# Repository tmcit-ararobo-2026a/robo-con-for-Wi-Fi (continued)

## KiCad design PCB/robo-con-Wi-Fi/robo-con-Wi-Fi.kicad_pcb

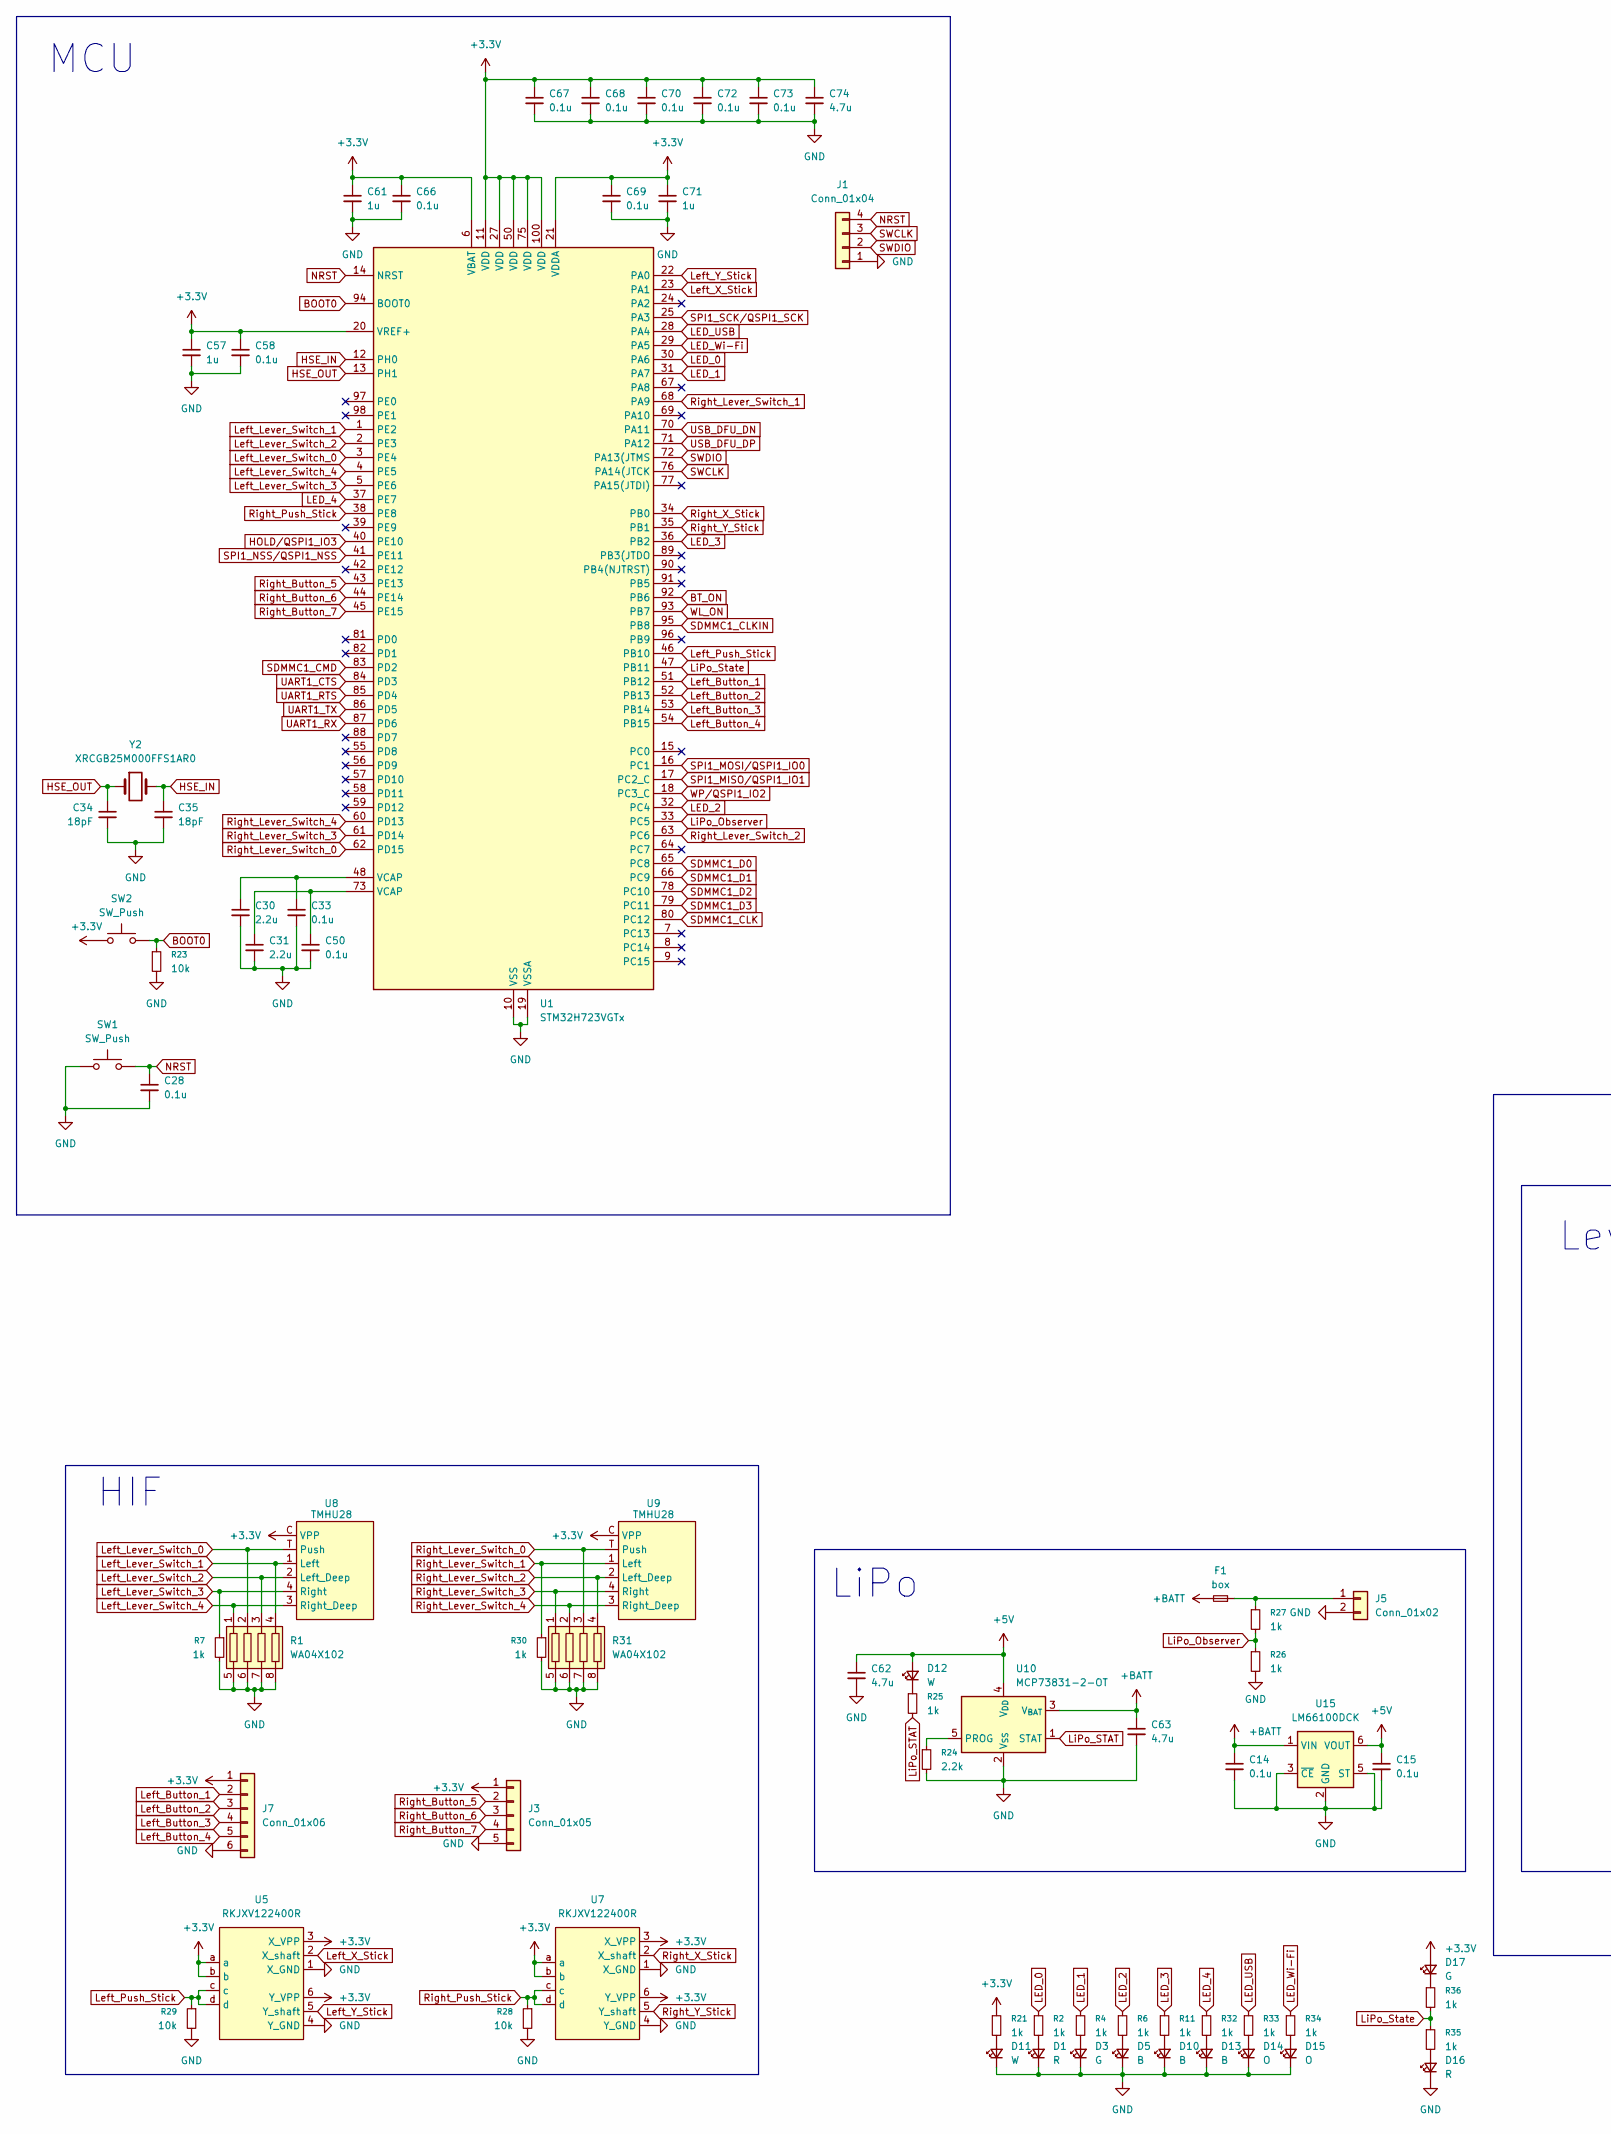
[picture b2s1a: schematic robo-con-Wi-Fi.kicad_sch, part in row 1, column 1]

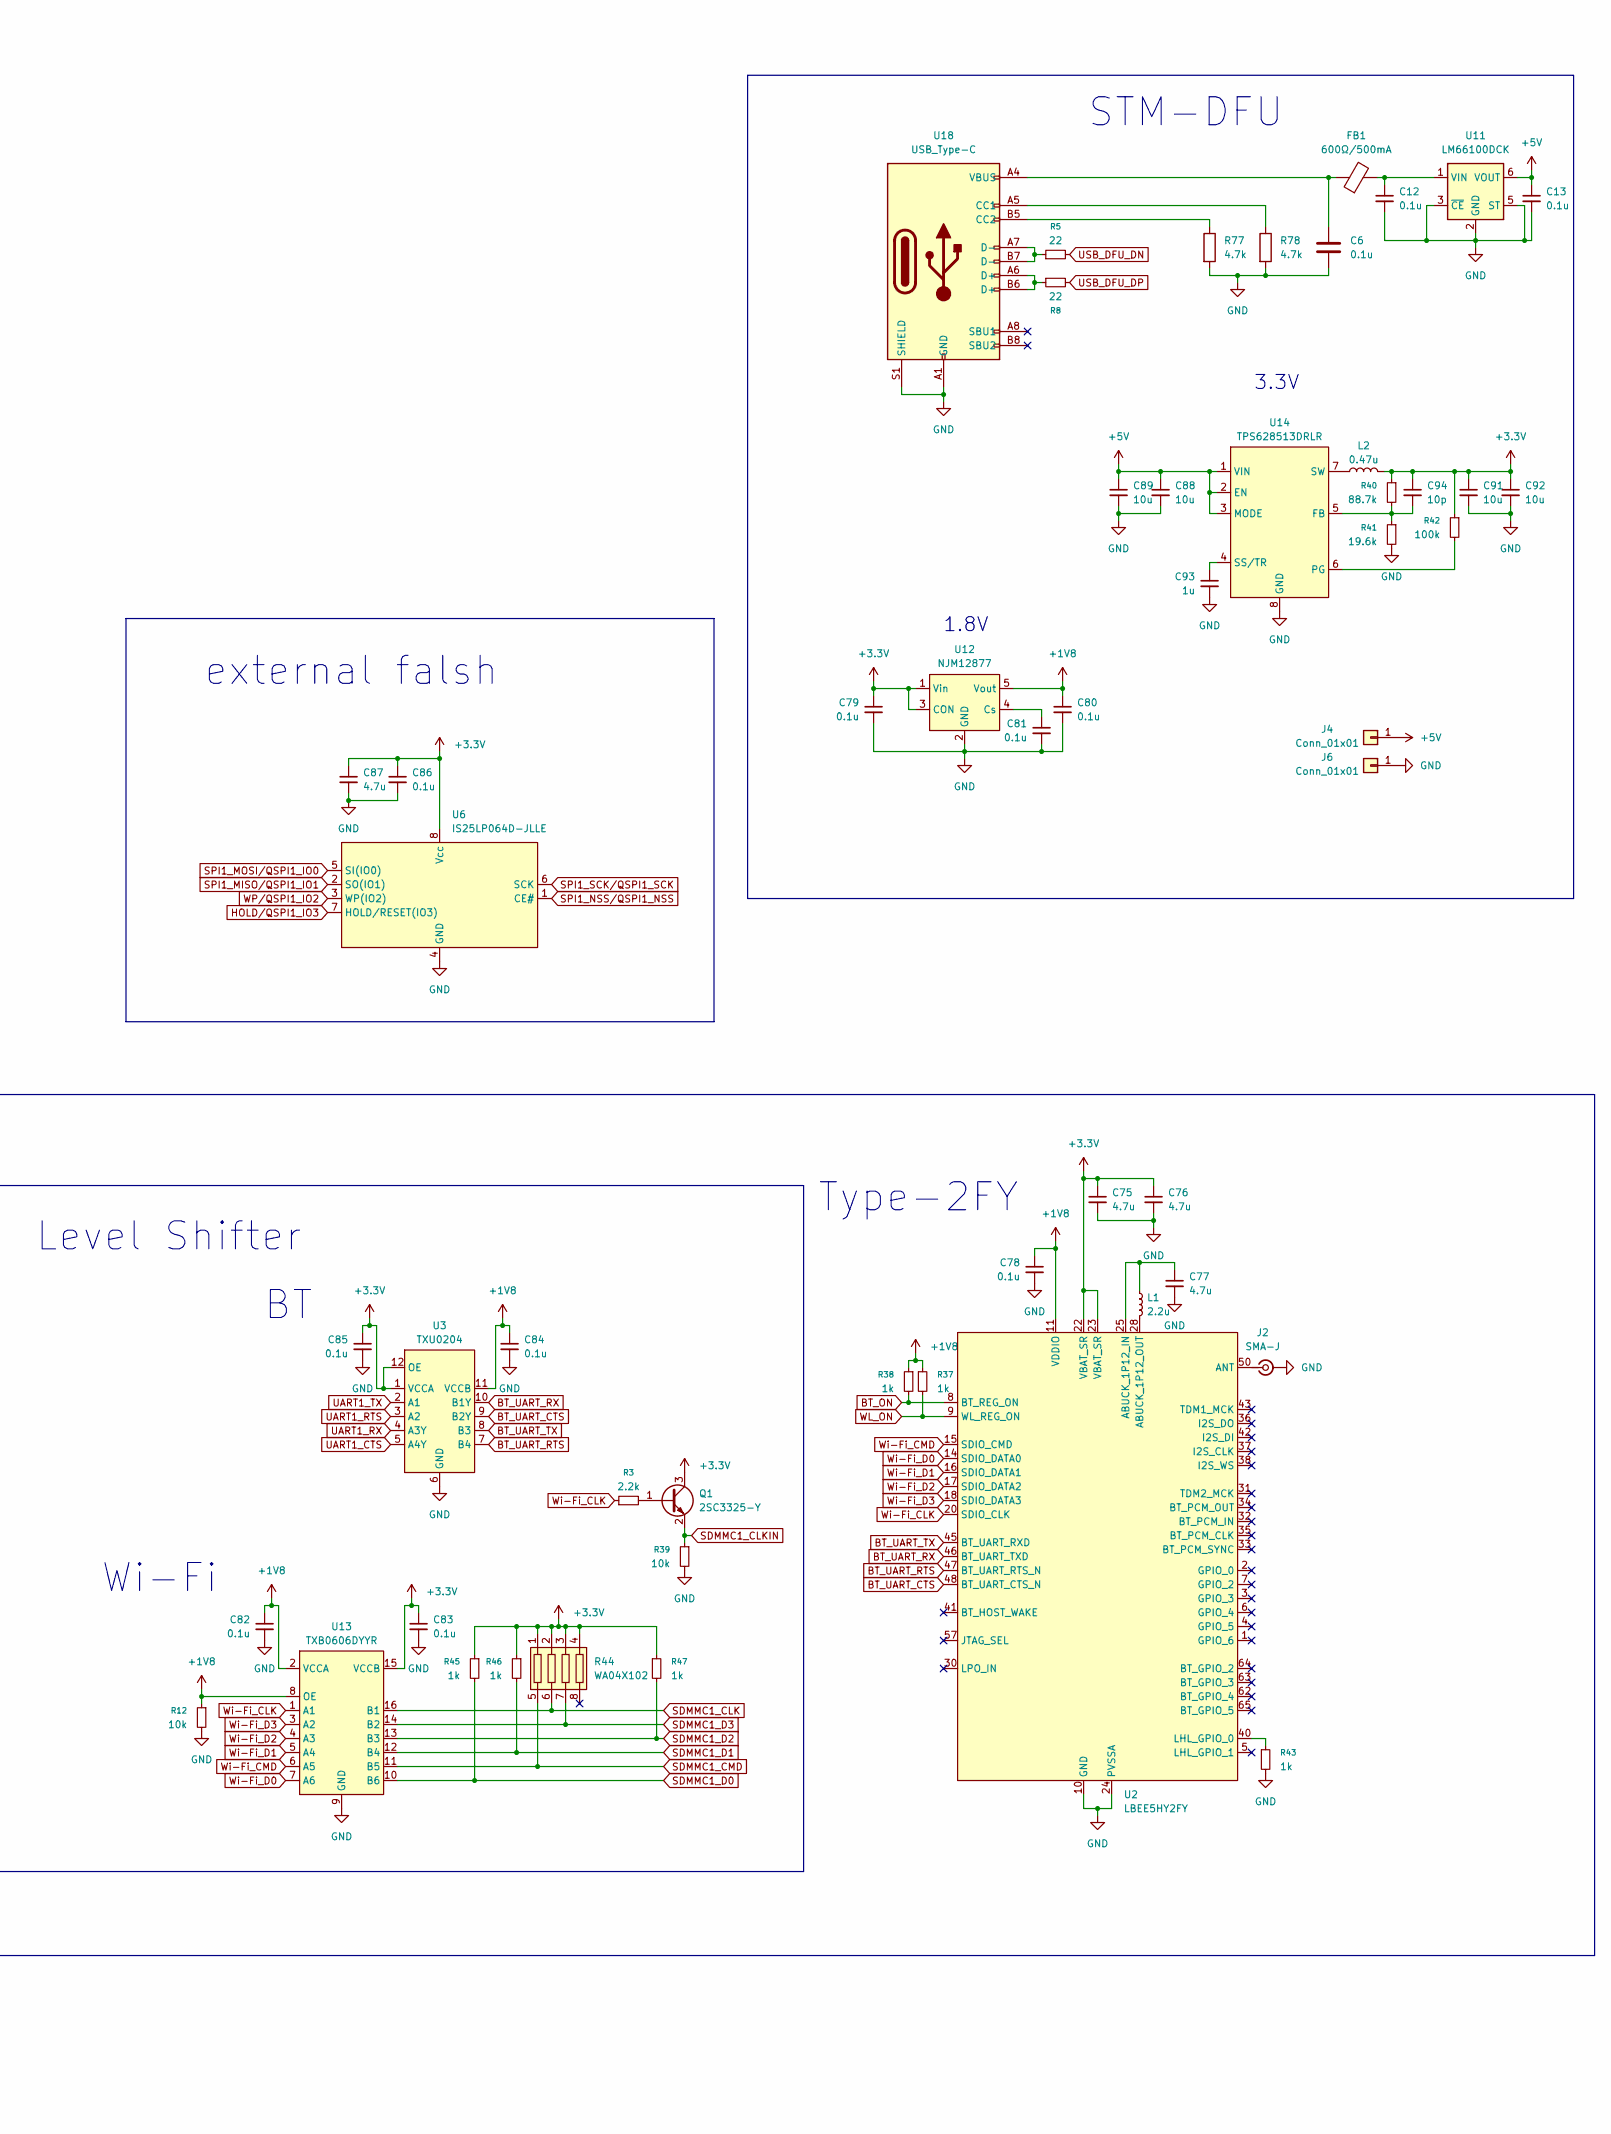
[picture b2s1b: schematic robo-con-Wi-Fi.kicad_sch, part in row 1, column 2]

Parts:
C6, C12, C13, C14, C15, C28, C33, C50, C58, C66, C67, C68, C69, C70, C72, C73, C78, C79, C80, C81, C82, C83, C84, C85, C86: 0.1u; C_0402_1005Metric_Pad0.74x0.62mm_HandSolder
C30, C31: 2.2u; C_0402_1005Metric_Pad0.74x0.62mm_HandSolder
C34, C35: 18pF; C_0402_1005Metric_Pad0.74x0.62mm_HandSolder
C57, C61, C71, C93: 1u; C_0402_1005Metric_Pad0.74x0.62mm_HandSolder
C62, C63, C74, C75, C76, C77, C87: 4.7u; C_0402_1005Metric_Pad0.74x0.62mm_HandSolder
C88, C89, C91, C92: 10u; C_0603_1608Metric_Pad1.08x0.95mm_HandSolder
C94: 10p; C_0402_1005Metric_Pad0.74x0.62mm_HandSolder
D1, D16: R; D_0603_1608Metric_Pad1.05x0.95mm_HandSolder
D3, D17: G; D_0603_1608Metric_Pad1.05x0.95mm_HandSolder
D5, D10, D13: B; D_0603_1608Metric_Pad1.05x0.95mm_HandSolder
D11, D12: W; D_0603_1608Metric_Pad1.05x0.95mm_HandSolder
D14, D15: O; D_0603_1608Metric_Pad1.05x0.95mm_HandSolder
F1: box; L_0603_1608Metric_Pad1.05x0.95mm_HandSolder
FB1: 600Ω/500mA; C_0603_1608Metric_Pad1.08x0.95mm_HandSolder
J1: Conn_01x04; PinSocket_1x04_P2.54mm_Horizontal
J2: SMA-J; SMA_Conn
J3: Conn_01x05; JST_ZH_B5B-ZR_1x05_P1.50mm_Vertical
J4, J6: Conn_01x01; SolderWirePad_1x01_SMD_1.5x3mm
J5: Conn_01x02; JST_PH_S2B-PH-K_1x02_P2.00mm_Horizontal
J7: Conn_01x06; JST_ZH_B6B-ZR_1x06_P1.50mm_Vertical
L1: 2.2u; L_1008_2520Metric_Pad1.43x2.20mm_HandSolder
L2: 0.47u; L_0603_1608Metric_Pad1.05x0.95mm_HandSolder
Q1: 2SC3325-Y; SC-59
R1, R31, R44: WA04X102
R2, R4, R6, R7, R11, R21, R25, R30, R32, R33, R34, R35, R36, R37, R38, R43, R45, R46, R47: 1k; R_0402_1005Metric_Pad0.72x0.64mm_HandSolder
R3: 2.2k; R_0402_1005Metric_Pad0.72x0.64mm_HandSolder
R5, R8: 22; R_0402_1005Metric_Pad0.72x0.64mm_HandSolder
R12, R23, R39: 10k; R_0402_1005Metric_Pad0.72x0.64mm_HandSolder
R24: 2.2k; R_0603_1608Metric_Pad0.98x0.95mm_HandSolder
R26, R27: 1k; R_0603_1608Metric_Pad0.98x0.95mm_HandSolder
R28, R29: 10k; R_0603_1608Metric_Pad0.98x0.95mm_HandSolder
R40: 88.7k; R_0402_1005Metric_Pad0.72x0.64mm_HandSolder
R41: 19.6k; R_0402_1005Metric_Pad0.72x0.64mm_HandSolder
R42: 100k; R_0402_1005Metric_Pad0.72x0.64mm_HandSolder
R77, R78: 4.7k; R_0402_1005Metric_Pad0.72x0.64mm_HandSolder
SW1, SW2: SW_Push; switch_TVAF06-A020B-R
U1: STM32H723VGTx; LQFP-100_14x14mm_P0.5mm
U2: LBEE5HY2FY
U3: TXU0204; UQFN-12
U5, U7: RKJXV122400R
U6: IS25LP064D-JLLE; WSON-8-1EP_8x6mm_P1.27mm_EP3.4x4.3mm
U8, U9: TMHU28
U10: MCP73831-2-OT; SOT-23-5
U11, U15: LM66100DCK; SOT-363_SC-70-6
U12: NJM12877; SOT-23-5_HandSoldering
U13: TXB0606DYYR; Texas_DYY0016A_TSOT-23-16_2x4.2mm_P0.5mm
U14: TPS628513DRLR; SOT-583-8
U18: USB_Type-C; USB_C_Receptacle_Nelton_5077CR-16-SMC2-BK-TR
Y2: XRCGB25M000FFS1AR0

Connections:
+1V8: C78.1, C80.1, C82.1, C84.1, R12.1, R37.1, R38.1, U2.11 (VDDIO), U3.11 (VCCB), U12.5 (Vout), U13.2 (VCCA), U13.8 (OE)
+3.3V: C57.1, C58.1, C61.1, C66.1, C67.1, C68.1, C69.1, C70.1, C71.1, C72.1, C73.1, C74.1, C75.1, C76.1, C79.1, C83.1, C85.1, C86.1, C87.1, C91.1, C92.1, C94.1, D17.2 (A), J3.1, J7.1, L2.2, Q1.3 (C), R21.1, R40.1, R42.1, R44.1, R44.2, R44.3, R44.4, R45.1, R46.1, R47.1, SW2.1, U1.6 (VBAT), U1.11 (VDD), U1.20 (VREF+), U1.21 (VDDA), U1.27 (VDD), U1.50 (VDD), U1.75 (VDD), U1.100 (VDD), U2.22 (VBAT_SR), U2.23 (VBAT_SR), U3.1 (VCCA), U3.12 (OE), U5.3 (X_VPP), U5.6 (Y_VPP), U5.a, U5.b, U6.8 (Vcc), U7.3 (X_VPP), U7.6 (Y_VPP), U7.a, U7.b, U8.C (VPP), U9.C (VPP), U12.1 (Vin), U12.3 (CON), U13.15 (VCCB)
+5V: C13.1, C15.1, C62.1, C88.1, C89.1, D12.2 (A), J4.1 (Pin_1_1), U10.4 (V_{DD}), U11.6 (VOUT), U14.1 (VIN), U14.2 (EN), U14.3 (MODE), U15.6 (VOUT)
+BATT: C14.1, C63.1, F1.2, U10.3 (V_{BAT}), U15.1 (VIN)
BOOT0: R23.1, SW2.2, U1.94 (BOOT0)
BT_ON: R38.2, U1.92 (PB6), U2.8 (BT_REG_ON)
BT_UART_CTS: U2.48 (BT_UART_CTS_N), U3.9 (B2Y)
BT_UART_RTS: U2.47 (BT_UART_RTS_N), U3.7 (B4)
BT_UART_RX: U2.46 (BT_UART_TXD), U3.10 (B1Y)
BT_UART_TX: U2.45 (BT_UART_RXD), U3.8 (B3)
GND: C6.2, C12.2, C13.2, C14.2, C15.2, C28.2, C30.2, C31.2, C33.2, C34.2, C35.2, C50.2, C57.2, C58.2, C61.2, C62.2, C63.2, C66.2, C67.2, C68.2, C69.2, C70.2, C71.2, C72.2, C73.2, C74.2, C75.2, C76.2, C77.2, C78.2, C79.2, C80.2, C81.2, C82.2, C83.2, C84.2, C85.2, C86.2, C87.2, C88.2, C89.2, C91.2, C92.2, C93.2, D1.1 (K), D3.1 (K), D5.1 (K), D10.1 (K), D11.1 (K), D13.1 (K), D14.1 (K), D15.1 (K), D16.1 (K), J1.1, J2.2 (Ext), J3.5, J5.2, J6.1 (Pin_1_1), J7.6, R1.5, R1.6, R1.7, R1.8, R7.2, R12.2, R23.2, R24.2, R26.2, R28.2, R29.2, R30.2, R31.5, R31.6, R31.7, R31.8, R39.2, R41.2, R43.2, R77.2, R78.2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
HOLD/QSPI1_IO3: U1.40 (PE10), U6.7 (HOLD/RESET(IO3))
HSE_IN: C35.1, U1.12 (PH0), Y2.3 (2)
HSE_OUT: C34.1, U1.13 (PH1), Y2.1
LED_0: R2.1, U1.30 (PA6)
LED_1: R4.1, U1.31 (PA7)
LED_2: R6.1, U1.32 (PC4)
LED_3: R11.1, U1.36 (PB2)
LED_4: R32.1, U1.37 (PE7)
LED_USB: R33.1, U1.28 (PA4)
LED_Wi-Fi: R34.1, U1.29 (PA5)
Left_Button_1: J7.2, U1.51 (PB12)
Left_Button_2: J7.3, U1.52 (PB13)
Left_Button_3: J7.4, U1.53 (PB14)
Left_Button_4: J7.5, U1.54 (PB15)
Left_Lever_Switch_0: R1.2, U1.3 (PE4), U8.T (Push)
Left_Lever_Switch_1: R1.4, U1.1 (PE2), U8.1 (Left)
Left_Lever_Switch_2: R1.3, U1.2 (PE3), U8.2 (Left_Deep)
Left_Lever_Switch_3: R7.1, U1.5 (PE6), U8.4 (Right)
Left_Lever_Switch_4: R1.1, U1.4 (PE5), U8.3 (Right_Deep)
Left_Push_Stick: R29.1, U1.46 (PB10), U5.c, U5.d
Left_X_Stick: U1.23 (PA1), U5.2 (X_shaft)
Left_Y_Stick: U1.22 (PA0), U5.5 (Y_shaft)
LiPo_Observer: R26.1, R27.2, U1.33 (PC5)
LiPo_STAT: R25.2, U10.1 (STAT)
LiPo_State: R35.1, R36.2, U1.47 (PB11)
NRST: C28.1, J1.4, SW1.2, U1.14 (NRST)
unnamed: C6.1, FB1.1, U18.A4 (VBUS), U18.B4 (VBUS)
unnamed: C30.1, C33.1, U1.48 (VCAP)
unnamed: C31.1, C50.1, U1.73 (VCAP)
unnamed: D1.2 (A), R2.2
unnamed: D3.2 (A), R4.2
unnamed: D5.2 (A), R6.2
unnamed: D10.2 (A), R11.2
unnamed: D11.2 (A), R21.2
unnamed: D12.1 (K), R25.1
unnamed: D13.2 (A), R32.2
unnamed: D14.2 (A), R33.2
unnamed: D15.2 (A), R34.2
unnamed: D16.2 (A), R35.2
unnamed: D17.1 (K), R36.1
unnamed: J2.1 (In), U2.50 (ANT)
unnamed: F1.1, J5.1, R27.1
unnamed: Q1.1 (B), R3.2
unnamed: R5.1, U18.A7 (D-), U18.B7 (D-)
unnamed: R8.1, U18.A6 (D+), U18.B6 (D+)
unnamed: C77.1, L1.1, U2.25 (ABUCK_1P12_IN)
unnamed: L1.2, U2.28 (ABUCK_1P12_OUT)
unnamed: R43.1, U2.40 (LHL_GPIO_0)
unnamed: R24.1, U10.5 (PROG)
unnamed: C12.1, FB1.2, U11.1 (VIN)
unnamed: C81.1, U12.4 (Cs)
unnamed: C94.2, R40.2, R41.1, U14.5 (FB)
unnamed: R42.2, U14.6 (PG)
unnamed: C93.1, U14.4 (SS/TR)
unnamed: L2.1, U14.7 (SW)
unnamed: R78.1, U18.A5 (CC1)
unnamed: R77.1, U18.B5 (CC2)
Right_Button_5: J3.2, U1.43 (PE13)
Right_Button_6: J3.3, U1.44 (PE14)
Right_Button_7: J3.4, U1.45 (PE15)
Right_Lever_Switch_0: R31.3, U1.62 (PD15), U9.T (Push)
Right_Lever_Switch_1: R30.1, U1.68 (PA9), U9.1 (Left)
Right_Lever_Switch_2: R31.4, U1.63 (PC6), U9.2 (Left_Deep)
Right_Lever_Switch_3: R31.1, U1.61 (PD14), U9.4 (Right)
Right_Lever_Switch_4: R31.2, U1.60 (PD13), U9.3 (Right_Deep)
Right_Push_Stick: R28.1, U1.38 (PE8), U7.c, U7.d
Right_X_Stick: U1.34 (PB0), U7.2 (X_shaft)
Right_Y_Stick: U1.35 (PB1), U7.5 (Y_shaft)
SDMMC1_CLK: R44.6, U1.80 (PC12), U13.16 (B1)
SDMMC1_CLKIN: Q1.2 (E), R39.1, U1.95 (PB8)
SDMMC1_CMD: R44.5, U1.83 (PD2), U13.11 (B5)
SDMMC1_D0: R45.2, U1.65 (PC8), U13.10 (B6)
SDMMC1_D1: R46.2, U1.66 (PC9), U13.12 (B4)
SDMMC1_D2: R47.2, U1.78 (PC10), U13.13 (B3)
SDMMC1_D3: R44.7, U1.79 (PC11), U13.14 (B2)
SPI1_MISO/QSPI1_IO1: U1.17 (PC2_C), U6.2 (SO(IO1))
SPI1_MOSI/QSPI1_IO0: U1.16 (PC1), U6.5 (SI(IO0))
SPI1_NSS/QSPI1_NSS: U1.41 (PE11), U6.1 (CE#)
SPI1_SCK/QSPI1_SCK: U1.25 (PA3), U6.6 (SCK)
SWCLK: J1.3, U1.76 (PA14(JTCK)
SWDIO: J1.2, U1.72 (PA13(JTMS)
UART1_CTS: U1.84 (PD3), U3.5 (A4Y)
UART1_RTS: U1.85 (PD4), U3.3 (A2)
UART1_RX: U1.87 (PD6), U3.4 (A3Y)
UART1_TX: U1.86 (PD5), U3.2 (A1)
USB_DFU_DN: R5.2, U1.70 (PA11)
USB_DFU_DP: R8.2, U1.71 (PA12)
WL_ON: R37.2, U1.93 (PB7), U2.9 (WL_REG_ON)
WP/QSPI1_IO2: U1.18 (PC3_C), U6.3 (WP(IO2))
Wi-Fi_CLK: R3.1, U2.20 (SDIO_CLK), U13.1 (A1)
Wi-Fi_CMD: U2.15 (SDIO_CMD), U13.6 (A5)
Wi-Fi_D0: U2.14 (SDIO_DATA0), U13.7 (A6)
Wi-Fi_D1: U2.16 (SDIO_DATA1), U13.5 (A4)
Wi-Fi_D2: U2.17 (SDIO_DATA2), U13.4 (A3)
Wi-Fi_D3: U2.18 (SDIO_DATA3), U13.3 (A2)

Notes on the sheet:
Type-2FY
LiPo
Level Shifter
1.8V
Wi-Fi
external falsh
STM-DFU
3.3V
MCU
HIF

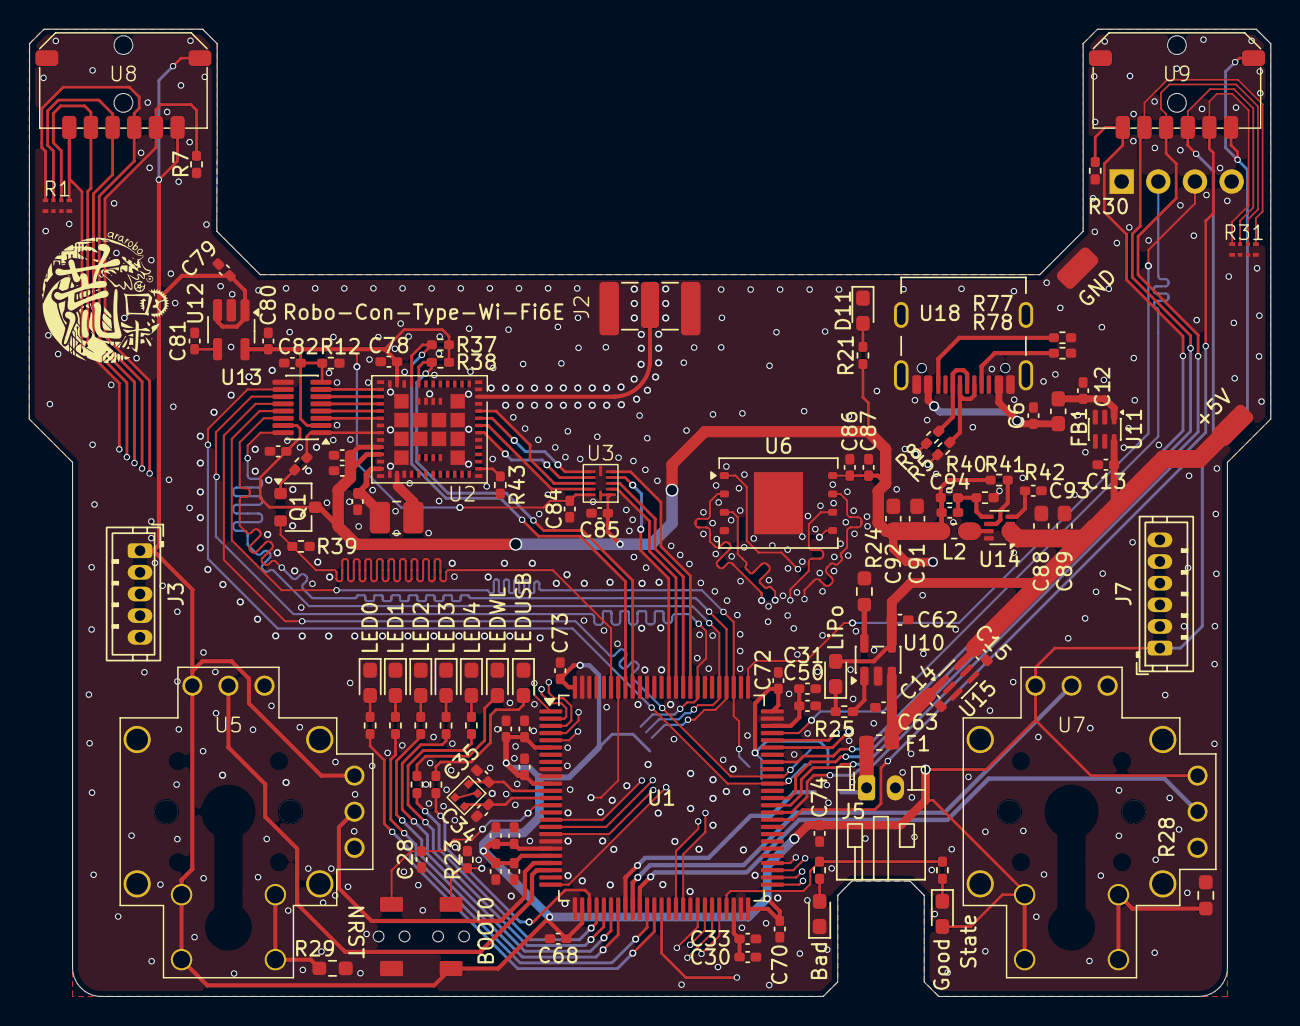
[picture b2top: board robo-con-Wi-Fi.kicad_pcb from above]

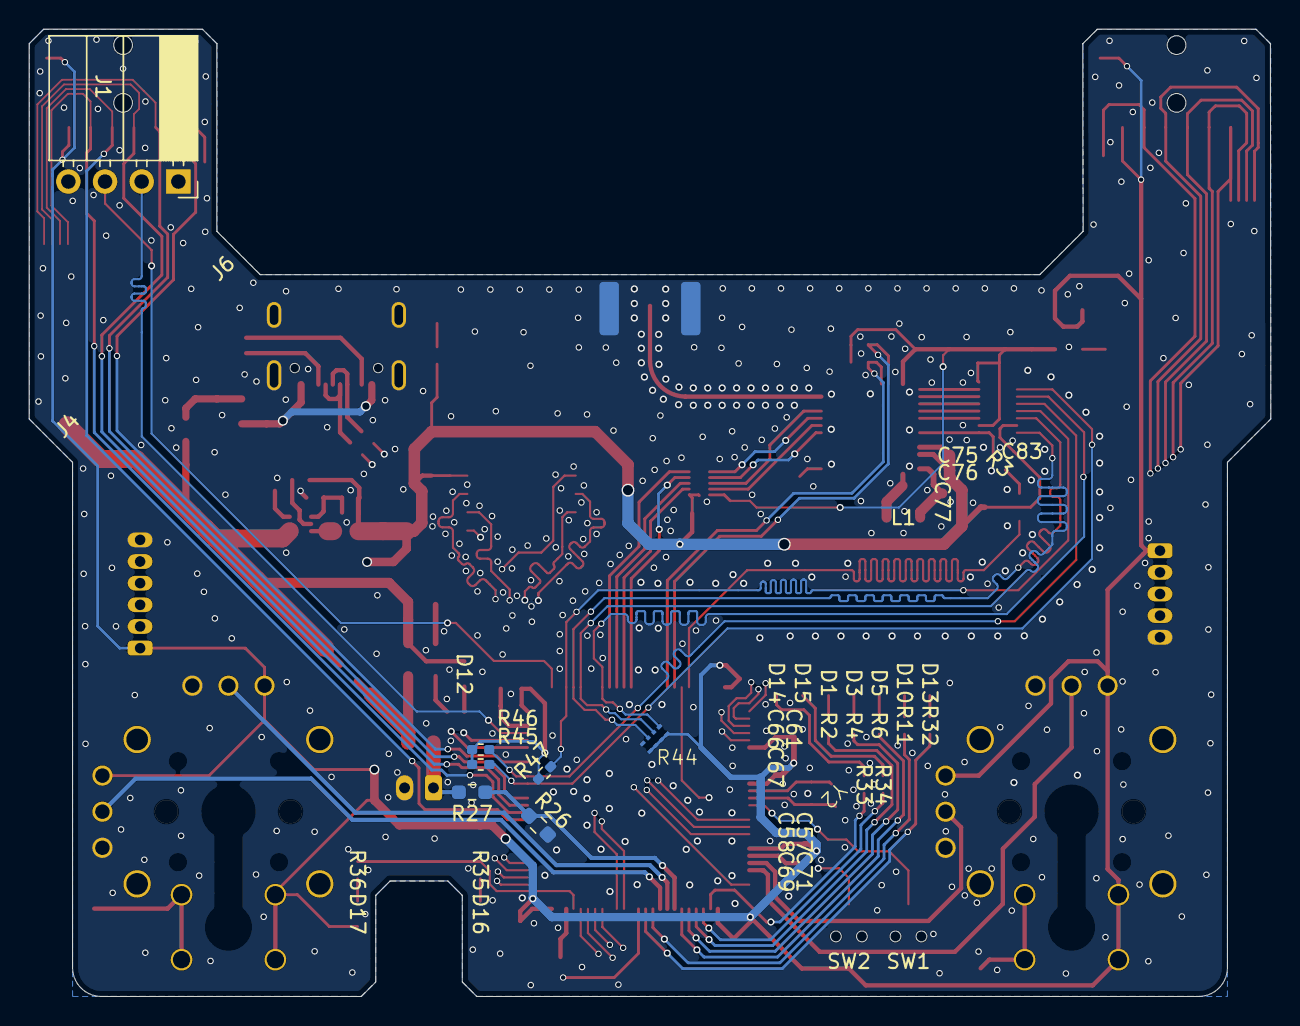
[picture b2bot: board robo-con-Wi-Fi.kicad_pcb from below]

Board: 4 copper layers, 86.0 x 67.0 mm, 124 parts (7 on the bottom side), 106 nets.

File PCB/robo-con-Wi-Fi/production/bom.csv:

Designator,Footprint,Quantity,Value,LCSC Part #
"C12, C13, C14, C15, C28, C33, C50, C58, C6, C66, C67, C68, C69, C70, C72, C73, C78, C79, C80, C81, C82, C83, C84, C85, C86",0402,25,0.1u,
"C30, C31",0402,2,2.2u,
"C34, C35",0402,2,18pF,
"C57, C61, C71, C93",0402,4,1u,
"C62, C63, C74, C75, C76, C77, C87",0402,7,4.7u,
"C88, C89, C91, C92",0603,4,10u,
C94,0402,1,10p,
"D1, D16",0603,2,R,
"D10, D13, D5",0603,3,B,
"D11, D12",0603,2,W,
"D14, D15",0603,2,O,
"D17, D3",0603,2,G,
F1,0603,1,box,
FB1,0603,1,600Ω/500mA,
J1,PinSocket_1x04_P2.54mm_Horizontal,1,Conn_01x04,
J2,SMA_Conn,1,SMA-J,
J3,JST_ZH_B5B-ZR_1x05_P1.50mm_Vertical,1,Conn_01x05,
"J4, J6",SolderWirePad_1x01_SMD_1.5x3mm,2,Conn_01x01,
J5,JST_PH_S2B-PH-K_1x02_P2.00mm_Horizontal,1,Conn_01x02,
J7,JST_ZH_B6B-ZR_1x06_P1.50mm_Vertical,1,Conn_01x06,
L1,1008,1,2.2u,
L2,0603,1,0.47u,
Q1,SC-59,1,2SC3325-Y,
"R1, R31, R44",WA04X102,3,WA04X102,
"R11, R2, R21, R25, R30, R32, R33, R34, R35, R36, R37, R38, R4, R43, R45, R46, R47, R6, R7",0402,19,1k,
"R12, R23, R39",0402,3,10k,
R24,0603,1,2.2k,
"R26, R27",0603,2,1k,
"R28, R29",0603,2,10k,
R3,0402,1,2.2k,
R40,0402,1,88.7k,
R41,0402,1,19.6k,
R42,0402,1,100k,
"R5, R8",0402,2,22,
"R77, R78",0402,2,4.7k,
"SW1, SW2",switch_TVAF06-A020B-R,2,SW_Push,
U1,LQFP-100_14x14mm_P0.5mm,1,STM32H723VGTx,
U10,SOT-23-5,1,MCP73831-2-OT,
"U11, U15",SOT-363_SC-70-6,2,LM66100DCK,
U12,SOT-23-5_HandSoldering,1,NJM12877,
U13,Texas_DYY0016A_TSOT-23-16_2x4.2mm_P0.5mm,1,TXB0606DYYR,
U14,SOT-583-8,1,TPS628513DRLR,
U18,USB_C_Receptacle_Nelton_5077CR-16-SMC2-BK-TR,1,USB_Type-C,
U2,LBEE5HY2FY,1,LBEE5HY2FY,
U3,UQFN-12,1,TXU0204,
"U5, U7",RKJXV122400R,2,RKJXV122400R,
U6,WSON-8-1EP_8x6mm_P1.27mm_EP3.4x4.3mm,1,IS25LP064D-JLLE,
"U8, U9",TMHU28,2,TMHU28,
Y2,XRCGB25M000FFS1AR0,1,XRCGB25M000FFS1AR0,

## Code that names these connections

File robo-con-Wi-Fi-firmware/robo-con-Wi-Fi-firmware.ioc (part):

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Mcu.Name=STM32H723VGTx
Mcu.Package=LQFP100
Mcu.UserName=STM32H723VGTx
PA0.GPIOParameters=GPIO_Label
PA0.GPIO_Label=STICK_Y_L
PA0.Mode=IN16-Single-Ended
PA0.Signal=ADC1_INP16
PA1.GPIOParameters=GPIO_Label
PA1.GPIO_Label=STICK_X_L
PA1.Mode=IN17-Single-Ended
PA1.Signal=ADC1_INP17
PA11.Mode=Device_Only_FS
PA11.Signal=USB_OTG_HS_DM
PA12.Mode=Device_Only_FS
PA12.Signal=USB_OTG_HS_DP
PA13(JTMS/SWDIO).Mode=Serial_Wire
PA13(JTMS/SWDIO).Signal=DEBUG_JTMS-SWDIO
PA14(JTCK/SWCLK).Mode=Serial_Wire
PA14(JTCK/SWCLK).Signal=DEBUG_JTCK-SWCLK
PA3.Mode=O1_P1_CLK
PA3.Signal=OCTOSPIM_P1_CLK
PA4.GPIOParameters=GPIO_Label
PA4.GPIO_Label=LED_USB
PA4.Signal=GPIO_Output
PA5.GPIOParameters=GPIO_Label
PA5.GPIO_Label=LED_Wi-Fi
PA5.Signal=GPIO_Output
PA6.GPIOParameters=GPIO_Label
PA6.GPIO_Label=LED4
PA6.Signal=GPIO_Output
PA7.GPIOParameters=GPIO_Label
PA7.GPIO_Label=LED3
PA7.Signal=GPIO_Output
PA9.GPIOParameters=GPIO_Label
PA9.GPIO_Label=LEVER_R1
PA9.Signal=GPIO_Input
PB0.GPIOParameters=GPIO_Label
PB0.GPIO_Label=STICK_X_R
PB0.Signal=ADCx_INP9
PB1.GPIOParameters=GPIO_Label
PB1.GPIO_Label=STICK_Y_R
PB1.Signal=ADCx_INP5
PB10.GPIOParameters=GPIO_Label
PB10.GPIO_Label=STICK_PUSH_L
PB10.Signal=GPIO_Input
PB11.GPIOParameters=GPIO_Label
PB11.GPIO_Label=LIPO_STATE
PB11.Signal=GPIO_Output
PB12.GPIOParameters=GPIO_Label
PB12.GPIO_Label=BUTTON_L1
PB12.Signal=GPIO_Input
PB13.GPIOParameters=GPIO_Label
PB13.GPIO_Label=BUTTON_L2
PB13.Signal=GPIO_Input
PB14.GPIOParameters=GPIO_Label
PB14.GPIO_Label=BUTTON_L3
PB14.Signal=GPIO_Input
PB15.GPIOParameters=GPIO_Label
PB15.GPIO_Label=BUTTON_L4
PB15.Signal=GPIO_Input
PB2.GPIOParameters=GPIO_Label
PB2.GPIO_Label=LED1
PB2.Signal=GPIO_Output
PB6.GPIOParameters=GPIO_PuPd,GPIO_Label,GPIO_ModeDefaultOutputPP
PB6.GPIO_Label=BT_ON
PB6.GPIO_ModeDefaultOutputPP=GPIO_MODE_OUTPUT_OD
PB6.GPIO_PuPd=GPIO_NOPULL
PB6.Signal=GPIO_Output
PB7.GPIOParameters=GPIO_PuPd,GPIO_Label,GPIO_ModeDefaultOutputPP
PB7.GPIO_Label=WL_ON
PB7.GPIO_ModeDefaultOutputPP=GPIO_MODE_OUTPUT_OD
PB7.GPIO_PuPd=GPIO_NOPULL
PB7.Signal=GPIO_Output
PB8.Signal=SDMMC1_CKIN
PC1.Mode=OCTOSPI1_IOL_Port1H
PC1.Signal=OCTOSPIM_P1_IO4
PC10.Mode=SD_4_bits_Wide_bus
PC10.Signal=SDMMC1_D2
PC11.Mode=SD_4_bits_Wide_bus
PC11.Signal=SDMMC1_D3
PC12.Mode=SD_4_bits_Wide_bus
PC12.Signal=SDMMC1_CK
PC2_C.Mode=OCTOSPI1_IOL_Port1H
PC2_C.Signal=OCTOSPIM_P1_IO5
PC3_C.Mode=OCTOSPI1_IOL_Port1H
PC3_C.Signal=OCTOSPIM_P1_IO6
PC4.GPIOParameters=GPIO_Label
PC4.GPIO_Label=LED2
PC4.Signal=GPIO_Output
PC5.GPIOParameters=GPIO_Label
PC5.GPIO_Label=LIPO_OBSERVER
PC5.Signal=ADCx_INP8
PC6.GPIOParameters=GPIO_Label
PC6.GPIO_Label=LEVER_R2
PC6.Signal=GPIO_Input
PC8.Mode=SD_4_bits_Wide_bus
PC8.Signal=SDMMC1_D0
PC9.Mode=SD_4_bits_Wide_bus
PC9.Signal=SDMMC1_D1
PD13.GPIOParameters=GPIO_Label
PD13.GPIO_Label=LEVER_R4
PD13.Signal=GPIO_Input
PD14.GPIOParameters=GPIO_Label
PD14.GPIO_Label=LEVER_R3
PD14.Signal=GPIO_Input
PD15.GPIOParameters=GPIO_Label
PD15.GPIO_Label=LEVER_R0
PD15.Signal=GPIO_Input
PD2.Mode=SD_4_bits_Wide_bus
PD2.Signal=SDMMC1_CMD
PD3.Mode=CTS_RTS
PD3.Signal=USART2_CTS
PD4.Mode=CTS_RTS
PD4.Signal=USART2_RTS
PD5.Mode=Asynchronous
PD5.Signal=USART2_TX
PD6.Mode=Asynchronous
PD6.Signal=USART2_RX
PE10.Mode=OCTOSPI1_IOL_Port1H
PE10.Signal=OCTOSPIM_P1_IO7
PE11.Mode=OCTOSPI1_Port1_NCS
PE11.Signal=OCTOSPIM_P1_NCS
PE13.GPIOParameters=GPIO_Label
PE13.GPIO_Label=BUTTON_R5
PE13.Signal=GPIO_Input
PE14.GPIOParameters=GPIO_Label
PE14.GPIO_Label=BUTTON_R6
PE14.Signal=GPIO_Input
PE15.GPIOParameters=GPIO_Label
PE15.GPIO_Label=BUTTON_R7
PE15.Signal=GPIO_Input
PE2.GPIOParameters=GPIO_Label
PE2.GPIO_Label=LEVER_L1
PE2.Signal=GPIO_Input
PE3.GPIOParameters=GPIO_Label
PE3.GPIO_Label=LEVER_L2
PE3.Signal=GPIO_Input
PE4.GPIOParameters=GPIO_Label
PE4.GPIO_Label=LEVER_L0
PE4.Signal=GPIO_Input
PE5.GPIOParameters=GPIO_Label
PE5.GPIO_Label=LEVER_L4
PE5.Signal=GPIO_Input
PE6.GPIOParameters=GPIO_Label
PE6.GPIO_Label=LEVER_L3
PE6.Signal=GPIO_Input
PE7.GPIOParameters=GPIO_Label
PE7.GPIO_Label=LED0
PE7.Signal=GPIO_Output
PE8.GPIOParameters=GPIO_Label
PE8.GPIO_Label=STICK_PUSH_R
PE8.Signal=GPIO_Input
PH0-OSC_IN.Mode=HSE-External-Oscillator
PH0-OSC_IN.Signal=RCC_OSC_IN
PH1-OSC_OUT.Mode=HSE-External-Oscillator
PH1-OSC_OUT.Signal=RCC_OSC_OUT
RCC.HSE_VALUE=25000000
RCC.SYSCLKFreq_VALUE=550000000
RCC.SYSCLKSource=RCC_SYSCLKSOURCE_PLLCLK
board=custom

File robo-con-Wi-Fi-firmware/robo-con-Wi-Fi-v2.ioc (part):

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Mcu.Name=STM32H723VGTx
Mcu.Package=LQFP100
Mcu.UserName=STM32H723VGTx
PA10.Mode=Asynchronous
PA10.Signal=USART1_RX
PA11.Mode=CTS_RTS
PA11.Signal=USART1_CTS
PA12.Mode=CTS_RTS
PA12.Signal=USART1_RTS
PA13(JTMS/SWDIO).Mode=Serial_Wire
PA13(JTMS/SWDIO).Signal=DEBUG_JTMS-SWDIO
PA14(JTCK/SWCLK).Mode=Serial_Wire
PA14(JTCK/SWCLK).Signal=DEBUG_JTCK-SWCLK
PA4.GPIOParameters=GPIO_Label
PA4.GPIO_Label=LY_STICK
PA4.Signal=ADCx_INP18
PA5.GPIOParameters=GPIO_Label
PA5.GPIO_Label=LX_STICK
PA5.Signal=ADCx_INP19
PA6.GPIOParameters=GPIO_PuPd,GPIO_Label
PA6.GPIO_Label=LP_STICK
PA6.GPIO_PuPd=GPIO_PULLDOWN
PA6.Signal=GPIO_Input
PA9.Mode=Asynchronous
PA9.Signal=USART1_TX
PB0.GPIOParameters=GPIO_Label
PB0.GPIO_Label=RX_STICK
PB0.Signal=ADCx_INP9
PB1.GPIOParameters=GPIO_Label
PB1.GPIO_Label=RY_STICK
PB1.Signal=ADCx_INP5
PB11.GPIOParameters=GPIO_PuPd,GPIO_Label
PB11.GPIO_Label=RP_STICK
PB11.GPIO_PuPd=GPIO_PULLDOWN
PB11.Signal=GPIO_Input
PB12.GPIOParameters=GPIO_PuPd,GPIO_Label
PB12.GPIO_Label=R1_BUTTON
PB12.GPIO_PuPd=GPIO_PULLDOWN
PB12.Signal=GPIO_Input
PB13.GPIOParameters=GPIO_PuPd,GPIO_Label
PB13.GPIO_Label=R2_BUTTON
PB13.GPIO_PuPd=GPIO_PULLDOWN
PB13.Signal=GPIO_Input
PB14.GPIOParameters=GPIO_PuPd,GPIO_Label
PB14.GPIO_Label=R3_BUTTON
PB14.GPIO_PuPd=GPIO_PULLDOWN
PB14.Signal=GPIO_Input
PB15.GPIOParameters=GPIO_PuPd,GPIO_Label
PB15.GPIO_Label=R4_BUTTON
PB15.GPIO_PuPd=GPIO_PULLDOWN
PB15.Signal=GPIO_Input
PB3(JTDO/TRACESWO).GPIOParameters=PinState,GPIO_PuPd,GPIO_Label,GPIO_ModeDefaultOutputPP
PB3(JTDO/TRACESWO).GPIO_Label=LED0
PB3(JTDO/TRACESWO).GPIO_ModeDefaultOutputPP=GPIO_MODE_OUTPUT_OD
PB3(JTDO/TRACESWO).GPIO_PuPd=GPIO_NOPULL
PB3(JTDO/TRACESWO).PinState=GPIO_PIN_SET
PB3(JTDO/TRACESWO).Signal=GPIO_Output
PB4(NJTRST).GPIOParameters=PinState,GPIO_PuPd,GPIO_Label,GPIO_ModeDefaultOutputPP
PB4(NJTRST).GPIO_Label=LED1
PB4(NJTRST).GPIO_ModeDefaultOutputPP=GPIO_MODE_OUTPUT_OD
PB4(NJTRST).GPIO_PuPd=GPIO_NOPULL
PB4(NJTRST).PinState=GPIO_PIN_SET
PB4(NJTRST).Signal=GPIO_Output
PB5.GPIOParameters=PinState,GPIO_PuPd,GPIO_Label,GPIO_ModeDefaultOutputPP
PB5.GPIO_Label=LED2
PB5.GPIO_ModeDefaultOutputPP=GPIO_MODE_OUTPUT_OD
PB5.GPIO_PuPd=GPIO_NOPULL
PB5.PinState=GPIO_PIN_SET
PB5.Signal=GPIO_Output
PB6.GPIOParameters=PinState,GPIO_PuPd,GPIO_Label,GPIO_ModeDefaultOutputPP
PB6.GPIO_Label=LED3
PB6.GPIO_ModeDefaultOutputPP=GPIO_MODE_OUTPUT_OD
PB6.GPIO_PuPd=GPIO_NOPULL
PB6.PinState=GPIO_PIN_SET
PB6.Signal=GPIO_Output
PB7.GPIOParameters=PinState,GPIO_PuPd,GPIO_Label,GPIO_ModeDefaultOutputPP
PB7.GPIO_Label=LED4
PB7.GPIO_ModeDefaultOutputPP=GPIO_MODE_OUTPUT_OD
PB7.GPIO_PuPd=GPIO_NOPULL
PB7.PinState=GPIO_PIN_SET
PB7.Signal=GPIO_Output
PB8.GPIOParameters=PinState,GPIO_PuPd,GPIO_Label,GPIO_ModeDefaultOutputPP
PB8.GPIO_Label=LEDWL
PB8.GPIO_ModeDefaultOutputPP=GPIO_MODE_OUTPUT_OD
PB8.GPIO_PuPd=GPIO_NOPULL
PB8.PinState=GPIO_PIN_SET
PB8.Signal=GPIO_Output
PB9.GPIOParameters=PinState,GPIO_PuPd,GPIO_Label,GPIO_ModeDefaultOutputPP
PB9.GPIO_Label=LEDUSB
PB9.GPIO_ModeDefaultOutputPP=GPIO_MODE_OUTPUT_OD
PB9.GPIO_PuPd=GPIO_NOPULL
PB9.PinState=GPIO_PIN_SET
PB9.Signal=GPIO_Output
PC0.GPIOParameters=GPIO_PuPd,GPIO_Label
PC0.GPIO_Label=L8_BUTTON
PC0.GPIO_PuPd=GPIO_PULLDOWN
PC0.Signal=GPIO_Input
PC10.Mode=SD_4_bits_Wide_bus
PC10.Signal=SDMMC1_D2
PC11.Mode=SD_4_bits_Wide_bus
PC11.Signal=SDMMC1_D3
PC12.Mode=SD_4_bits_Wide_bus
PC12.Signal=SDMMC1_CK
PC13.GPIOParameters=GPIO_PuPd,GPIO_Label
PC13.GPIO_Label=L5_BUTTON
PC13.GPIO_PuPd=GPIO_PULLDOWN
PC13.Signal=GPIO_Input
PC14-OSC32_IN.GPIOParameters=GPIO_PuPd,GPIO_Label
PC14-OSC32_IN.GPIO_Label=L6_BUTTON
PC14-OSC32_IN.GPIO_PuPd=GPIO_PULLDOWN
PC14-OSC32_IN.Signal=GPIO_Input
PC15-OSC32_OUT.GPIOParameters=GPIO_PuPd,GPIO_Label
PC15-OSC32_OUT.GPIO_Label=L7_BUTTON
PC15-OSC32_OUT.GPIO_PuPd=GPIO_PULLDOWN
PC15-OSC32_OUT.Signal=GPIO_Input
PC5.GPIOParameters=GPIO_Label
PC5.GPIO_Label=LiPo_OBSERVE
PC5.Signal=ADCx_INP8
PC6.GPIOParameters=GPIO_PuPd,GPIO_Label
PC6.GPIO_Label=R1_LEVER
PC6.GPIO_PuPd=GPIO_PULLDOWN
PC6.Signal=GPIO_Input
PC8.Mode=SD_4_bits_Wide_bus
PC8.Signal=SDMMC1_D0
PC9.Mode=SD_4_bits_Wide_bus
PC9.Signal=SDMMC1_D1
PD10.GPIOParameters=GPIO_PuPd,GPIO_Label
PD10.GPIO_Label=R4_LEVER
PD10.GPIO_PuPd=GPIO_PULLDOWN
PD10.Signal=GPIO_Input
PD11.Mode=CTS_RTS
PD11.Signal=USART3_CTS
PD12.Mode=CTS_RTS
PD12.Signal=USART3_RTS
PD13.GPIOParameters=GPIO_PuPd,GPIO_Label
PD13.GPIO_Label=R3_LEVER
PD13.GPIO_PuPd=GPIO_PULLDOWN
PD13.Signal=GPIO_Input
PD14.GPIOParameters=GPIO_PuPd,GPIO_Label
PD14.GPIO_Label=R0_LEVER
PD14.GPIO_PuPd=GPIO_PULLDOWN
PD14.Signal=GPIO_Input
PD15.GPIOParameters=GPIO_PuPd,GPIO_Label
PD15.GPIO_Label=R2_LEVER
PD15.GPIO_PuPd=GPIO_PULLDOWN
PD15.Signal=GPIO_Input
PD2.Mode=SD_4_bits_Wide_bus
PD2.Signal=SDMMC1_CMD
PD5.GPIOParameters=PinState,GPIO_PuPd,GPIO_Label,GPIO_ModeDefaultOutputPP
PD5.GPIO_Label=WL_ON
PD5.GPIO_ModeDefaultOutputPP=GPIO_MODE_OUTPUT_OD
PD5.GPIO_PuPd=GPIO_NOPULL
PD5.PinState=GPIO_PIN_SET
PD5.Signal=GPIO_Output
PD6.GPIOParameters=PinState,GPIO_Label
PD6.GPIO_Label=BT_ON
PD6.PinState=GPIO_PIN_SET
PD6.Signal=GPIO_Output
PD8.Mode=Asynchronous
PD8.Signal=USART3_TX
PD9.Mode=Asynchronous
PD9.Signal=USART3_RX
PE0.GPIOParameters=PinState,GPIO_PuPd,GPIO_Label,GPIO_ModeDefaultOutputPP
PE0.GPIO_Label=LEDLiPo_GOOD
PE0.GPIO_ModeDefaultOutputPP=GPIO_MODE_OUTPUT_OD
PE0.GPIO_PuPd=GPIO_NOPULL
PE0.PinState=GPIO_PIN_SET
PE0.Signal=GPIO_Output
PE1.GPIOParameters=PinState,GPIO_PuPd,GPIO_Label,GPIO_ModeDefaultOutputPP
PE1.GPIO_Label=LEDLiPo_BAD
PE1.GPIO_ModeDefaultOutputPP=GPIO_MODE_OUTPUT_OD
PE1.GPIO_PuPd=GPIO_NOPULL
PE1.PinState=GPIO_PIN_SET
PE1.Signal=GPIO_Output
PE2.GPIOParameters=GPIO_PuPd,GPIO_Label
PE2.GPIO_Label=L0_LEVER
PE2.GPIO_PuPd=GPIO_PULLDOWN
PE2.Signal=GPIO_Input
PE3.GPIOParameters=GPIO_PuPd,GPIO_Label
PE3.GPIO_Label=L2_LEVER
PE3.GPIO_PuPd=GPIO_PULLDOWN
PE3.Signal=GPIO_Input
PE4.GPIOParameters=GPIO_PuPd,GPIO_Label
PE4.GPIO_Label=L1_LEVER
PE4.GPIO_PuPd=GPIO_PULLDOWN
PE4.Signal=GPIO_Input
PE5.GPIOParameters=GPIO_PuPd,GPIO_Label
PE5.GPIO_Label=L3_LEVER
PE5.GPIO_PuPd=GPIO_PULLDOWN
PE5.Signal=GPIO_Input
PE6.GPIOParameters=GPIO_PuPd,GPIO_Label
PE6.GPIO_Label=L4_LEVER
PE6.GPIO_PuPd=GPIO_PULLDOWN
PE6.Signal=GPIO_Input
PH0-OSC_IN.Mode=HSE-External-Oscillator
PH0-OSC_IN.Signal=RCC_OSC_IN
PH1-OSC_OUT.Mode=HSE-External-Oscillator
PH1-OSC_OUT.Signal=RCC_OSC_OUT
RCC.SYSCLKFreq_VALUE=550000000
RCC.SYSCLKSource=RCC_SYSCLKSOURCE_PLLCLK
board=custom

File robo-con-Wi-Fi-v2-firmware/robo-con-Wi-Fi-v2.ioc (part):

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Mcu.Name=STM32H7A3R(G-I)Tx
Mcu.Package=LQFP64
Mcu.UserName=STM32H7A3RGTx
PA0.Mode=CTS_RTS
PA0.Signal=USART2_CTS
PA1.Mode=CTS_RTS
PA1.Signal=USART2_RTS
PA10.Mode=Asynchronous
PA10.Signal=USART1_RX
PA11.Mode=CTS_RTS
PA11.Signal=USART1_CTS
PA12.Mode=CTS_RTS
PA12.Signal=USART1_RTS
PA13.Mode=Serial_Wire
PA13.Signal=DEBUG_JTMS-SWDIO
PA14.Mode=Serial_Wire
PA14.Signal=DEBUG_JTCK-SWCLK
PA15.GPIOParameters=PinState,GPIO_PuPd,GPIO_Label,GPIO_ModeDefaultOutputPP
PA15.GPIO_Label=LED1
PA15.GPIO_ModeDefaultOutputPP=GPIO_MODE_OUTPUT_OD
PA15.GPIO_PuPd=GPIO_NOPULL
PA15.PinState=GPIO_PIN_SET
PA15.Signal=GPIO_Output
PA2.Mode=Asynchronous
PA2.Signal=USART2_TX
PA3.Mode=Asynchronous
PA3.Signal=USART2_RX
PA4.Signal=ADCx_INP18
PA5.Signal=ADCx_INP19
PA6.Signal=ADCx_INP3
PA7.GPIOParameters=GPIO_PuPd,GPIO_Label
PA7.GPIO_Label=R1_BUTTON
PA7.GPIO_PuPd=GPIO_PULLDOWN
PA7.Signal=GPIO_Input
PA8.GPIOParameters=PinState,GPIO_PuPd,GPIO_Label,GPIO_ModeDefaultOutputPP
PA8.GPIO_Label=LED0
PA8.GPIO_ModeDefaultOutputPP=GPIO_MODE_OUTPUT_OD
PA8.GPIO_PuPd=GPIO_NOPULL
PA8.PinState=GPIO_PIN_SET
PA8.Signal=GPIO_Output
PA9.Mode=Asynchronous
PA9.Signal=USART1_TX
PB0.GPIOParameters=GPIO_PuPd,GPIO_Label
PB0.GPIO_Label=R4_BUTTON
PB0.GPIO_PuPd=GPIO_PULLDOWN
PB0.Signal=GPIO_Input
PB1.GPIOParameters=GPIO_PuPd,GPIO_Label
PB1.GPIO_Label=RP_STICK
PB1.GPIO_PuPd=GPIO_PULLDOWN
PB1.Signal=GPIO_Input
PB10.GPIOParameters=GPIO_PuPd,GPIO_Label
PB10.GPIO_Label=R_PUSH_HOME
PB10.GPIO_PuPd=GPIO_PULLDOWN
PB10.Signal=GPIO_Input
PB12.GPIOParameters=PinState,GPIO_PuPd,GPIO_Label,GPIO_ModeDefaultOutputPP
PB12.GPIO_Label=LEDLiPo
PB12.GPIO_ModeDefaultOutputPP=GPIO_MODE_OUTPUT_OD
PB12.GPIO_PuPd=GPIO_NOPULL
PB12.PinState=GPIO_PIN_SET
PB12.Signal=GPIO_Output
PB13.Mode=SD_4_bits_Wide_bus
PB13.Signal=SDMMC1_D0
PB15.GPIOParameters=GPIO_PuPd,GPIO_Label,GPIO_ModeDefaultOutputPP
PB15.GPIO_Label=BT_ON
PB15.GPIO_ModeDefaultOutputPP=GPIO_MODE_OUTPUT_OD
PB15.GPIO_PuPd=GPIO_NOPULL
PB15.Signal=GPIO_Output
PB2.GPIOParameters=GPIO_PuPd,GPIO_Label
PB2.GPIO_Label=R_PUSH
PB2.GPIO_PuPd=GPIO_PULLDOWN
PB2.Signal=GPIO_Input
PB3.GPIOParameters=PinState,GPIO_PuPd,GPIO_Label,GPIO_ModeDefaultOutputPP
PB3.GPIO_Label=LEDUSB
PB3.GPIO_ModeDefaultOutputPP=GPIO_MODE_OUTPUT_OD
PB3.GPIO_PuPd=GPIO_NOPULL
PB3.PinState=GPIO_PIN_SET
PB3.Signal=GPIO_Output
PB4.GPIOParameters=GPIO_PuPd,GPIO_Label
PB4.GPIO_Label=L8_BUTTON
PB4.GPIO_PuPd=GPIO_PULLDOWN
PB4.Signal=GPIO_Input
PB5.GPIOParameters=GPIO_PuPd,GPIO_Label
PB5.GPIO_Label=L7_BUTTON
PB5.GPIO_PuPd=GPIO_PULLDOWN
PB5.Signal=GPIO_Input
PB6.GPIOParameters=GPIO_PuPd,GPIO_Label
PB6.GPIO_Label=L6_BUTTON
PB6.GPIO_PuPd=GPIO_PULLDOWN
PB6.Signal=GPIO_Input
PB7.GPIOParameters=GPIO_PuPd,GPIO_Label
PB7.GPIO_Label=L5_BUTTON
PB7.GPIO_PuPd=GPIO_PULLDOWN
PB7.Signal=GPIO_Input
PB8.GPIOParameters=GPIO_PuPd,GPIO_Label
PB8.GPIO_Label=L_PUSH_HOME
PB8.GPIO_PuPd=GPIO_PULLDOWN
PB8.Signal=GPIO_Input
PB9.GPIOParameters=GPIO_PuPd,GPIO_Label
PB9.GPIO_Label=L_PUSH
PB9.GPIO_PuPd=GPIO_PULLDOWN
PB9.Signal=GPIO_Input
PC0.Signal=ADCx_INP10
PC1.Signal=ADCx_INP11
PC10.Mode=SD_4_bits_Wide_bus
PC10.Signal=SDMMC1_D2
PC11.Mode=SD_4_bits_Wide_bus
PC11.Signal=SDMMC1_D3
PC12.Mode=SD_4_bits_Wide_bus
PC12.Signal=SDMMC1_CK
PC13.GPIOParameters=GPIO_PuPd,GPIO_Label
PC13.GPIO_Label=LP_STICK
PC13.GPIO_PuPd=GPIO_PULLDOWN
PC13.Signal=GPIO_Input
PC14-OSC32_IN.GPIOParameters=PinState,GPIO_PuPd,GPIO_Label,GPIO_ModeDefaultOutputPP
PC14-OSC32_IN.GPIO_Label=LEDWL
PC14-OSC32_IN.GPIO_ModeDefaultOutputPP=GPIO_MODE_OUTPUT_OD
PC14-OSC32_IN.GPIO_PuPd=GPIO_NOPULL
PC14-OSC32_IN.PinState=GPIO_PIN_SET
PC14-OSC32_IN.Signal=GPIO_Output
PC15-OSC32_OUT.GPIOParameters=PinState,GPIO_PuPd,GPIO_Label,GPIO_ModeDefaultOutputPP
PC15-OSC32_OUT.GPIO_Label=LED2
PC15-OSC32_OUT.GPIO_ModeDefaultOutputPP=GPIO_MODE_OUTPUT_OD
PC15-OSC32_OUT.GPIO_PuPd=GPIO_NOPULL
PC15-OSC32_OUT.PinState=GPIO_PIN_SET
PC15-OSC32_OUT.Signal=GPIO_Output
PC2.GPIOParameters=PinState,GPIO_PuPd,GPIO_Label,GPIO_ModeDefaultOutputPP
PC2.GPIO_Label=LEDWLRX
PC2.GPIO_ModeDefaultOutputPP=GPIO_MODE_OUTPUT_OD
PC2.GPIO_PuPd=GPIO_NOPULL
PC2.PinState=GPIO_PIN_SET
PC2.Signal=GPIO_Output
PC3.GPIOParameters=PinState,GPIO_PuPd,GPIO_Label,GPIO_ModeDefaultOutputPP
PC3.GPIO_Label=LEDWLTX
PC3.GPIO_ModeDefaultOutputPP=GPIO_MODE_OUTPUT_OD
PC3.GPIO_PuPd=GPIO_NOPULL
PC3.PinState=GPIO_PIN_SET
PC3.Signal=GPIO_Output
PC4.GPIOParameters=GPIO_PuPd,GPIO_Label
PC4.GPIO_Label=R2_BUTTON
PC4.GPIO_PuPd=GPIO_PULLDOWN
PC4.Signal=GPIO_Input
PC5.GPIOParameters=GPIO_PuPd,GPIO_Label
PC5.GPIO_Label=R3_BUTTON
PC5.GPIO_PuPd=GPIO_PULLDOWN
PC5.Signal=GPIO_Input
PC6.GPIOParameters=PinState,GPIO_PuPd,GPIO_Label,GPIO_ModeDefaultOutputPP
PC6.GPIO_Label=WL_ON
PC6.GPIO_ModeDefaultOutputPP=GPIO_MODE_OUTPUT_OD
PC6.GPIO_PuPd=GPIO_NOPULL
PC6.PinState=GPIO_PIN_RESET
PC6.Signal=GPIO_Output
PC9.Mode=SD_4_bits_Wide_bus
PC9.Signal=SDMMC1_D1
PD2.Mode=SD_4_bits_Wide_bus
PD2.Signal=SDMMC1_CMD
PH0-OSC_IN.Mode=HSE-External-Oscillator
PH0-OSC_IN.Signal=RCC_OSC_IN
PH1-OSC_OUT.Mode=HSE-External-Oscillator
PH1-OSC_OUT.Signal=RCC_OSC_OUT
RCC.HSE_VALUE=25000000
RCC.SYSCLKFreq_VALUE=280000000
RCC.SYSCLKSource=RCC_SYSCLKSOURCE_PLLCLK
board=custom
